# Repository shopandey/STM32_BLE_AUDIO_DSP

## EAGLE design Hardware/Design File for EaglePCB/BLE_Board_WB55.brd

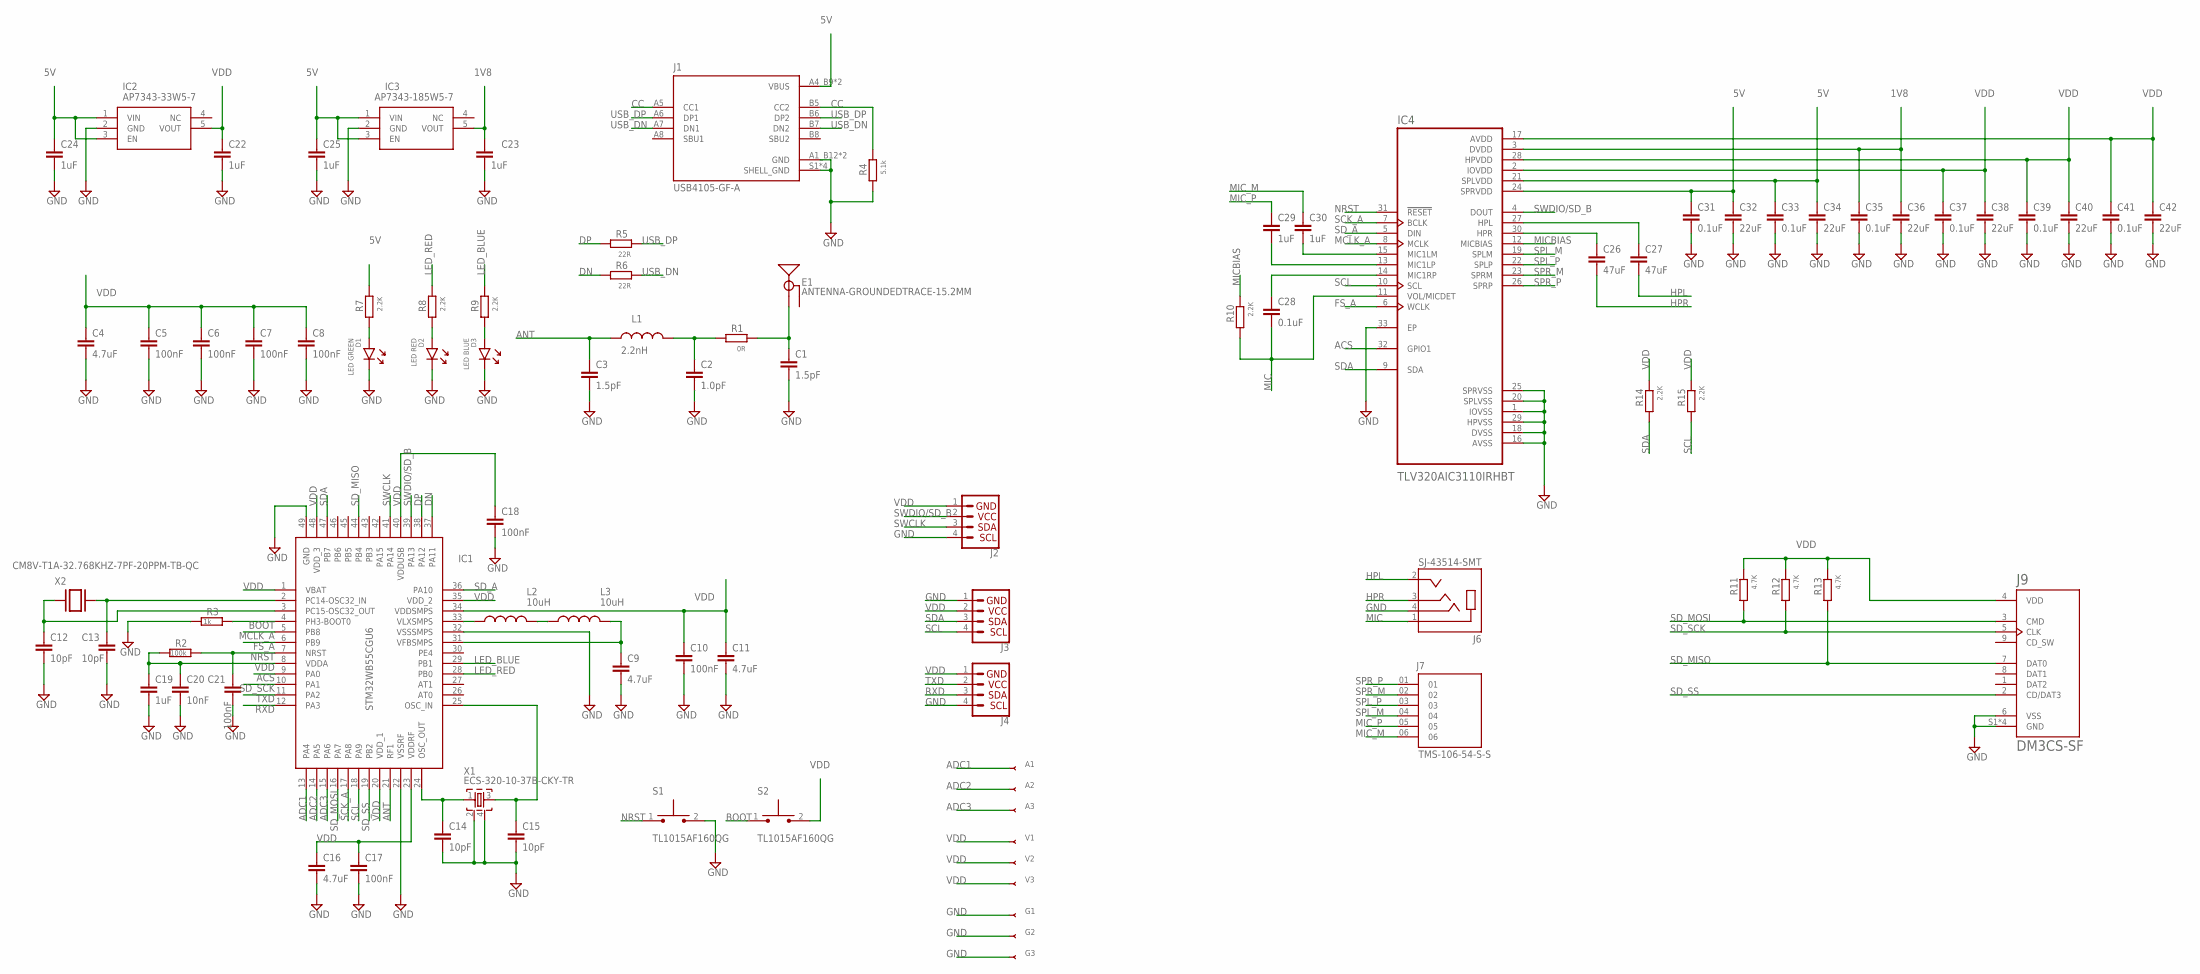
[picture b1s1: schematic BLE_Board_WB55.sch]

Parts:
A1, A2, A3: ATP-50
C1, C3: 1.5pF; RESC0402_N
C2: 1.0pF; RESC0402_N
C4, C9, C11, C16: 4.7uF; RESC0603_N
C5, C6, C7, C8, C10, C17, C18, C21: 100nF; RESC0603_N
C12, C13, C14, C15: 10pF; RESC0402_N
C19, C22, C23, C24, C25, C29, C30: 1uF; RESC0603_N
C20: 10nF; RESC0603_N
C26, C27: 47uF; RESC0603_N
C28, C31, C33, C35, C37, C39, C41: 0.1uF; RESC0603_N
C32, C34, C36, C38, C40, C42: 22uF; RESC0603_N
D1: LED GREEN; DIOC0603_N
D2: LED RED; DIOC0603_N
D3: LED BLUE; DIOC0603_N
E1: ANTENNA-GROUNDEDTRACE-15.2MM; TRACE_ANTENNA_2.4GHZ_15.2MM
G1, G2, G3: ATP-50
IC1: STM32WB55CGU6; QFN50P700X700X60-49N
IC2: AP7343-33W5-7; SOT95P285X140-5N
IC3: AP7343-185W5-7; SOT95P285X140-5N
IC4: TLV320AIC3110IRHBT; IC_ADS125H01IRHBT
J1: USB4105-GF-A; GCT_USB4105-GF-A
J2, J3, J4: QWIIC_CONNECTORJS-1MM; 1X04_1MM_RA
J6: SJ-43514-SMT; CUI_SJ-43514-SMT
J7: TMS-106-54-S-S; SAMTEC_TMS-106-54-S-S
J9: DM3CS-SF; HRS_DM3CS-SF
L1: 2.2nH; RESC0402_N
L2, L3: 10uH; RESC0603_N
R1: 0R; RESC0402_N
R2: 100k; RESC0603_N
R3: 1k; RESC0603_N
R4: 5.1k; RESC0603_N
R5, R6: 22R; RESC0603_N
R7, R8, R9, R10, R14, R15: 2.2K; RESC0603_N
R11, R12, R13: 4.7K; RESC0603_N
S1, S2: TL1015AF160QG; SW_TL1015AF160QG
V1, V2, V3: ATP-50
X1: ECS-320-10-37B-CKY-TR; BT-XTAL_2016_N
X2: CM8V-T1A-32.768KHZ-7PF-20PPM-TB-QC; XTAL_CM8V-T1A-32.768KHZ-7PF-20PPM-TB-QC

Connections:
1V8: C23.1, C35.1, C36.1, IC3.5 (VOUT), IC4.3 (DVDD)
5V: C24.1, C25.1, C31.1, C32.1, C33.1, C34.1, IC2.1 (VIN), IC2.3 (EN), IC3.1 (VIN), IC3.3 (EN), IC4.21 (SPLVDD), IC4.24 (SPRVDD), J1.A4_B9 (VBUS), J1.B4_A9 (VBUS), R7.1
ACS: IC1.9 (PA0), IC4.32 (GPIO1)
ADC1: A1.P, IC1.13 (PA4)
ADC2: A2.P, IC1.14 (PA5)
ADC3: A3.P, IC1.15 (PA6)
ANT: C3.1, IC1.21 (RF1), L1.1
BOOT: IC1.4 (PH3-BOOT0), R3.1, S2.1
CC: J1.A5 (CC1), J1.B5 (CC2), R4.1
DN: IC1.37 (PA11), R6.2
DP: IC1.38 (PA12), R5.2
FS_A: IC1.6 (PB9), IC4.6 (WCLK)
GND: C1.2, C2.2, C3.2, C4.2, C5.2, C6.2, C7.2, C8.2, C9.2, C10.2, C11.2, C12.2, C13.2, C14.2, C15.2, C16.2, C17.2, C18.2, C19.2, C20.2, C21.2, C22.2, C23.2, C24.2, C25.2, C31.2, C32.2, C33.2, C34.2, C35.2, C36.2, C37.2, C38.2, C39.2, C40.2, C41.2, C42.2, D1.1 (C), D2.1 (C), D3.1 (C), G1.P, G2.P, G3.P, IC1.22 (VSSRF), IC1.32 (VSSSMPS), IC1.49 (GND), IC2.2 (GND), IC3.2 (GND), IC4.1 (IOVSS), IC4.16 (AVSS), IC4.18 (DVSS), IC4.20 (SPLVSS), IC4.25 (SPRVSS), IC4.29 (HPVSS), IC4.33 (EP), J1.A1_B12 (GND), J1.B1_A12 (GND), J1.S1 (SHELL_GND), J1.S2 (SHELL_GND), J1.S3 (SHELL_GND), J1.S4 (SHELL_GND), J2.4, J3.1, J4.4, J6.4 (RING2), J9.6 (VSS), J9.S1 (GND), J9.S2 (GND), J9.S3 (GND), J9.S5 (GND), R3.2, R4.2, S1.2, X1.2, X1.4
HPL: C27.2, J6.2 (TIP)
HPR: C26.2, J6.3 (RING1)
LED_BLUE: IC1.29 (PB1), R9.1
LED_RED: IC1.28 (PB0), R8.1
MCLK_A: IC1.5 (PB8), IC4.8 (MCLK)
MIC: C28.2, IC4.11 (VOL/MICDET), J6.1 (SLEEVE), R10.2
MICBIAS: IC4.12 (MICBIAS), R10.1
MIC_M: C30.1, J7.06
MIC_P: C29.1, J7.05
unnamed: C1.1, E1.ANT (SIGNAL), R1.2
unnamed: C2.1, L1.2, R1.1
unnamed: IC1.33 (VLXSMPS), L2.1
unnamed: L2.2, L3.1
unnamed: C9.1, IC1.31 (VFBSMPS), L3.2
unnamed: C13.1, IC1.2 (PC14-OSC32_IN), X2.2
unnamed: C12.1, IC1.3 (PC15-OSC32_OUT), X2.1
unnamed: C14.1, IC1.24 (OSC_OUT), X1.1
unnamed: C15.1, IC1.25 (OSC_IN), X1.3
unnamed: D1.2 (A), R7.2
unnamed: C26.1, IC4.30 (HPR)
unnamed: C28.1, IC4.14 (MIC1RP)
unnamed: D3.2 (A), R9.2
unnamed: D2.2 (A), R8.2
unnamed: C27.1, IC4.27 (HPL)
unnamed: C30.2, IC4.15 (MIC1LM)
unnamed: C29.2, IC4.13 (MIC1LP)
NRST: C21.1, IC1.7 (NRST), IC4.31 (!RESET), R2.1, S1.1
RXD: IC1.12 (PA3), J4.3
SCK_A: IC1.17 (PA8), IC4.7 (BCLK)
SCL: IC1.18 (PA9), IC4.10 (SCL), J3.4, R15.2
SDA: IC1.47 (PB7), IC4.9 (SDA), J3.3, R14.2
SD_A: IC1.36 (PA10), IC4.5 (DIN)
SD_MISO: IC1.44 (PB4), J9.7 (DAT0), R13.2
SD_MOSI: IC1.16 (PA7), J9.3 (CMD), R11.2
SD_SCK: IC1.10 (PA1), J9.5 (CLK), R12.2
SD_SS: IC1.19 (PB2), J9.2 (CD/DAT3)
SPL_M: IC4.19 (SPLM), J7.04
SPL_P: IC4.22 (SPLP), J7.03
SPR_M: IC4.23 (SPRM), J7.02
SPR_P: IC4.26 (SPRP), J7.01
SWCLK: IC1.41 (PA14), J2.3
SWDIO/SD_B: IC1.39 (PA13), IC4.4 (DOUT), J2.2
TXD: IC1.11 (PA2), J4.2
USB_DN: J1.A7 (DN1), J1.B7 (DN2), R6.1
USB_DP: J1.A6 (DP1), J1.B6 (DP2), R5.1
VDD: C4.1, C5.1, C6.1, C7.1, C8.1, C10.1, C11.1, C16.1, C17.1, C18.1, C19.1, C20.1, C22.1, C37.1, C38.1, C39.1, C40.1, C41.1, C42.1, IC1.1 (VBAT), IC1.8 (VDDA), IC1.20 (VDD_1), IC1.23 (VDDRF), IC1.34 (VDDSMPS), IC1.35 (VDD_2), IC1.40 (VDDUSB), IC1.48 (VDD_3), IC2.5 (VOUT), IC4.2 (IOVDD), IC4.17 (AVDD), IC4.28 (HPVDD), J2.1, J3.2, J4.1, J9.4 (VDD), R2.2, R11.1, R12.1, R13.1, R14.1, R15.1, S2.2, V1.P, V2.P, V3.P

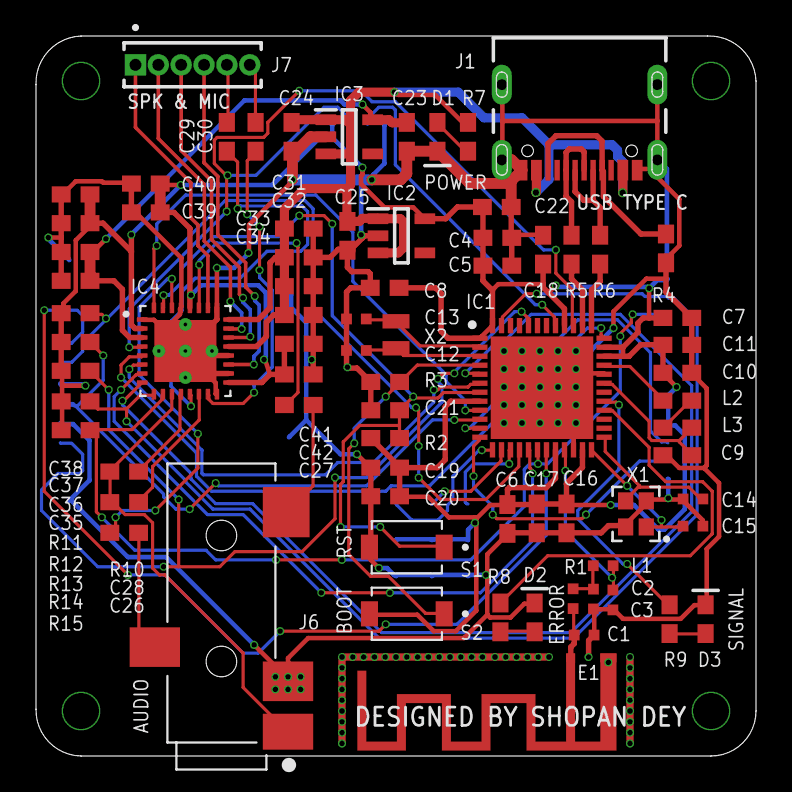
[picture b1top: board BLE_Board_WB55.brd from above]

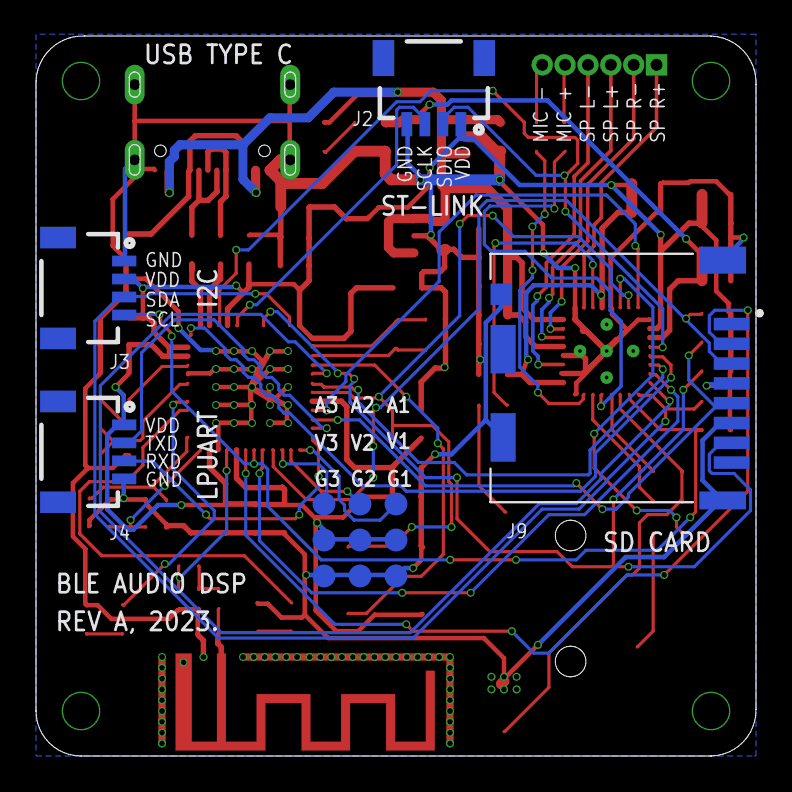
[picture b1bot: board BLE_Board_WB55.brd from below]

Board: 2 copper layers, 40.0 x 40.0 mm, 88 parts (13 on the bottom side), 59 nets.

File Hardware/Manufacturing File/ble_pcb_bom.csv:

Comment,Designator,Footprint,LCSC Part #
0.1uF,C28 C31 C33 C35 C37 C39 C41,RESC0603_N,
0R,R1,RESC0402_N,
1.0pF,C2,RESC0402_N,
1.5pF,C1 C3,RESC0402_N,
1k,R3,RESC0603_N,
1uF,C19 C22 C23 C24 C25 C29 C30,RESC0603_N,
2.2K,R7 R8 R9 R10 R14 R15,RESC0603_N,
2.2nH,L1,RESC0402_N,
4.7K,R11 R12 R13,RESC0603_N,
4.7uF,C4 C9 C11 C16,RESC0603_N,
5.1k,R4,RESC0603_N,
10nF,C20,RESC0603_N,
10pF,C12 C13 C14 C15,RESC0402_N,
10uH,L2 L3,RESC0603_N,
22R,R5 R6,RESC0603_N,
22uF,C32 C34 C36 C38 C40 C42,RESC0603_N,
47uF,C26 C27,RESC0603_N,
100k,R2,RESC0603_N,
100nF,C5 C6 C7 C8 C10 C17 C18 C21,RESC0603_N,
ANTENNA-GROUNDEDTRACE-15.2MM,E1,TRACE_ANTENNA_2.4GHZ_15.2MM,
AP7343-33W5-7,IC2,SOT95P285X140-5N,
AP7343-185W5-7,IC3,SOT95P285X140-5N,
CM8V-T1A-32.768KHZ-7PF-20PPM-TB-QC,X2,XTAL_CM8V-T1A-32.768KHZ-7PF-20PPM-TB-QC,
ECS-320-10-37B-CKY-TR,X1,BT-XTAL_2016_N,
LED BLUE,D3,DIOC0603_N,
LED GREEN,D1,DIOC0603_N,
LED RED,D2,DIOC0603_N,
SJ-43514-SMT,J6,CUI_SJ-43514-SMT,
STM32WB55CGU6,IC1,QFN50P700X700X60-49N,
TL1015AF160QG,S1 S2,SW_TL1015AF160QG,
TLV320AIC3110IRHBT,IC4,IC_ADS125H01IRHBT,
USB4105-GF-A,J1,GCT_USB4105-GF-A,
ATP-50,J2 J3 J4 A1 A2 A3 G1 G2 G3 V1 V2 V3,ATP-50,
DM3CS-SF,J9,HRS_DM3CS-SF,

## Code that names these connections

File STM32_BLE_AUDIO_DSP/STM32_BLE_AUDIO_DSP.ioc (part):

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Mcu.Name=STM32WB55CGUx
Mcu.Package=UFQFPN48
Mcu.UserName=STM32WB55CGUx
PA0.GPIOParameters=GPIO_PuPd,GPIO_Label
PA0.GPIO_Label=GPIO_Audio
PA0.GPIO_PuPd=GPIO_PULLUP
PA0.Signal=GPIO_Input
PA1.Mode=Full_Duplex_Master
PA1.Signal=SPI1_SCK
PA10.Mode=SAI_A_MasterWithClock
PA10.Signal=SAI1_SD_A
PA11.Mode=Device
PA11.Signal=USB_DM
PA12.Mode=Device
PA12.Signal=USB_DP
PA13.Mode=SAI_B_SyncSlave
PA13.Signal=SAI1_SD_B
PA2.Mode=Asynchronous
PA2.Signal=LPUART1_TX
PA3.Mode=Asynchronous
PA3.Signal=LPUART1_RX
PA4.GPIOParameters=GPIO_Label
PA4.GPIO_Label=VR1
PA4.Signal=ADCx_IN9
PA5.GPIOParameters=GPIO_Label
PA5.GPIO_Label=VR2
PA5.Signal=ADCx_IN10
PA6.GPIOParameters=GPIO_Label
PA6.GPIO_Label=VR3
PA6.Signal=ADCx_IN11
PA7.Mode=Full_Duplex_Master
PA7.Signal=SPI1_MOSI
PA8.Mode=SAI_A_MasterWithClock
PA8.Signal=SAI1_SCK_A
PA9.Mode=I2C
PA9.Signal=I2C1_SCL
PB0.GPIOParameters=GPIO_Label
PB0.GPIO_Label=LED_RED
PB0.Signal=GPIO_Output
PB1.GPIOParameters=GPIO_Label
PB1.GPIO_Label=LED_BLUE
PB1.Signal=GPIO_Output
PB2.Mode=NSS_Signal_Hard_Output
PB2.Signal=SPI1_NSS
PB4.Mode=Full_Duplex_Master
PB4.Signal=SPI1_MISO
PB7.Mode=I2C
PB7.Signal=I2C1_SDA
PB8.Mode=SAI_A_MasterWithClock
PB8.Signal=SAI1_MCLK_A
PB9.Mode=SAI_A_MasterWithClock
PB9.Signal=SAI1_FS_A
PC14-OSC32_IN.Mode=LSE-External-Oscillator
PC14-OSC32_IN.Signal=RCC_OSC32_IN
PC15-OSC32_OUT.Mode=LSE-External-Oscillator
PC15-OSC32_OUT.Signal=RCC_OSC32_OUT
RCC.HSE_VALUE=32000000
RCC.SYSCLKFreq_VALUE=64000000
RCC.SYSCLKSource=RCC_SYSCLKSOURCE_PLLCLK
board=custom

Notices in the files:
parts and their libraries:
SparkFun-RF: Licensing: Creative Commons ShareAlike 4.0 International - https://creativecommons.org/licenses/by-sa/4.0
testpoint: Copyright (C) 2008, Bob Starr
